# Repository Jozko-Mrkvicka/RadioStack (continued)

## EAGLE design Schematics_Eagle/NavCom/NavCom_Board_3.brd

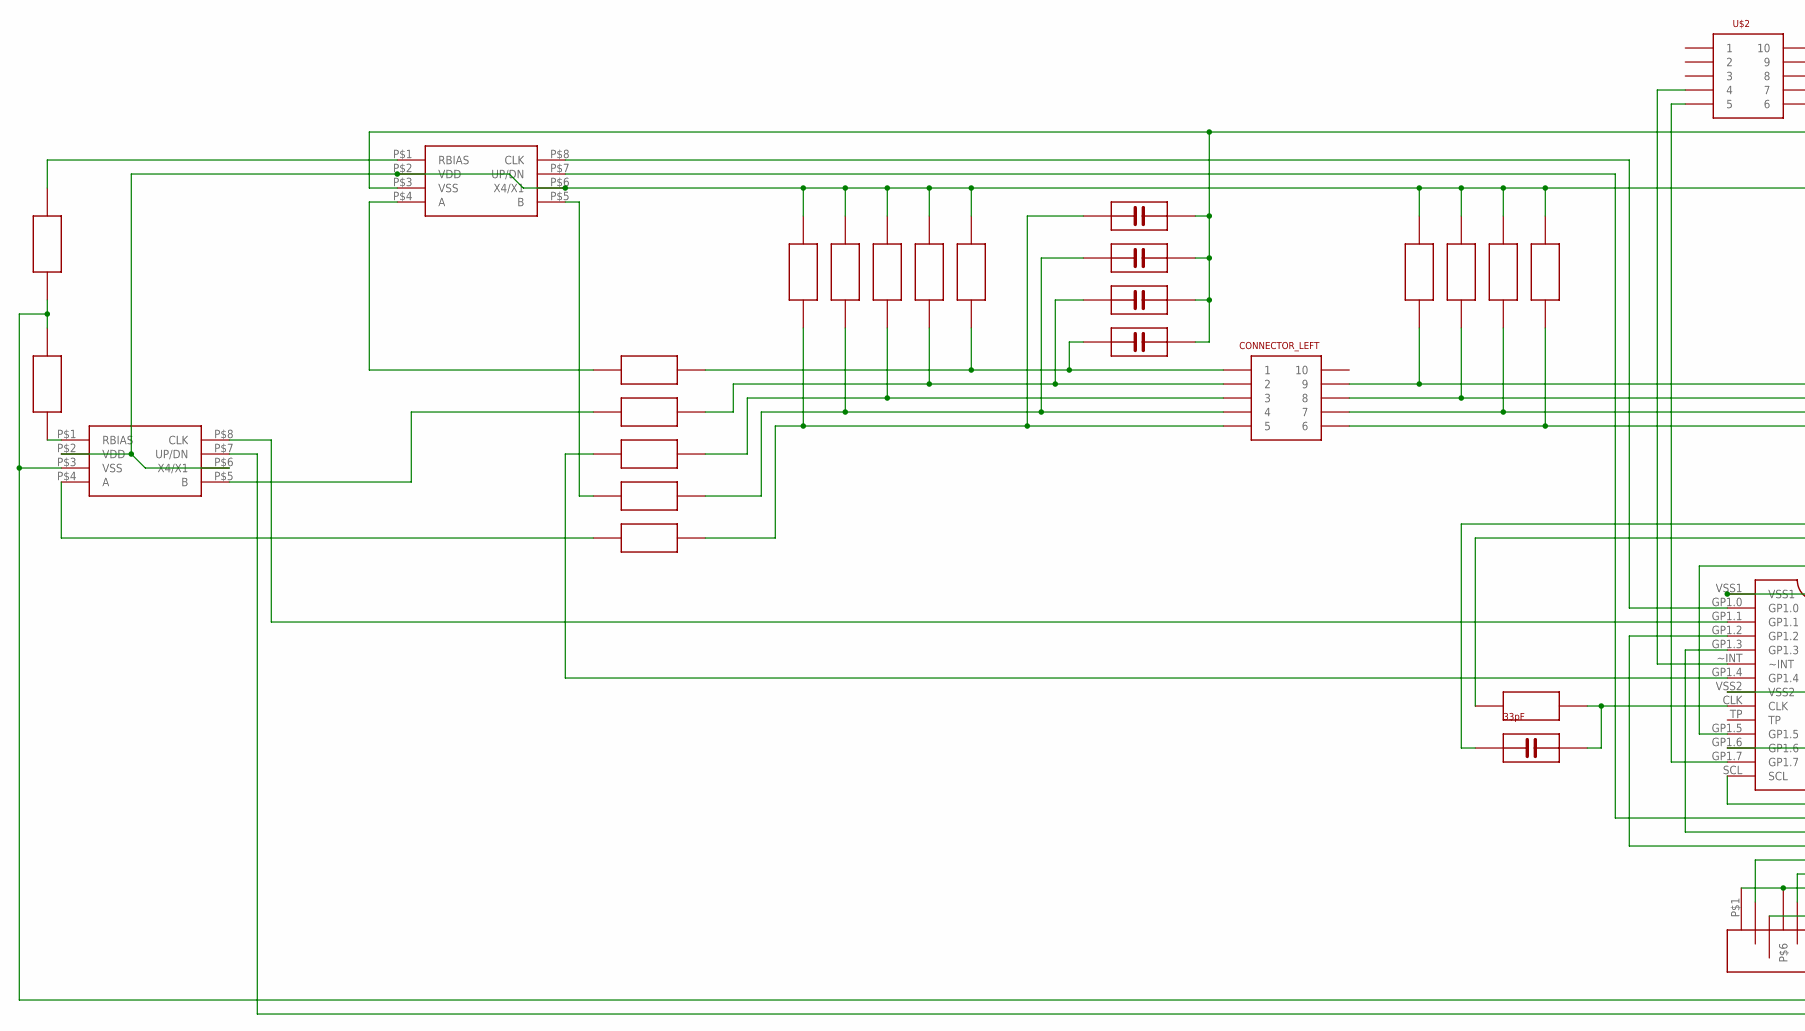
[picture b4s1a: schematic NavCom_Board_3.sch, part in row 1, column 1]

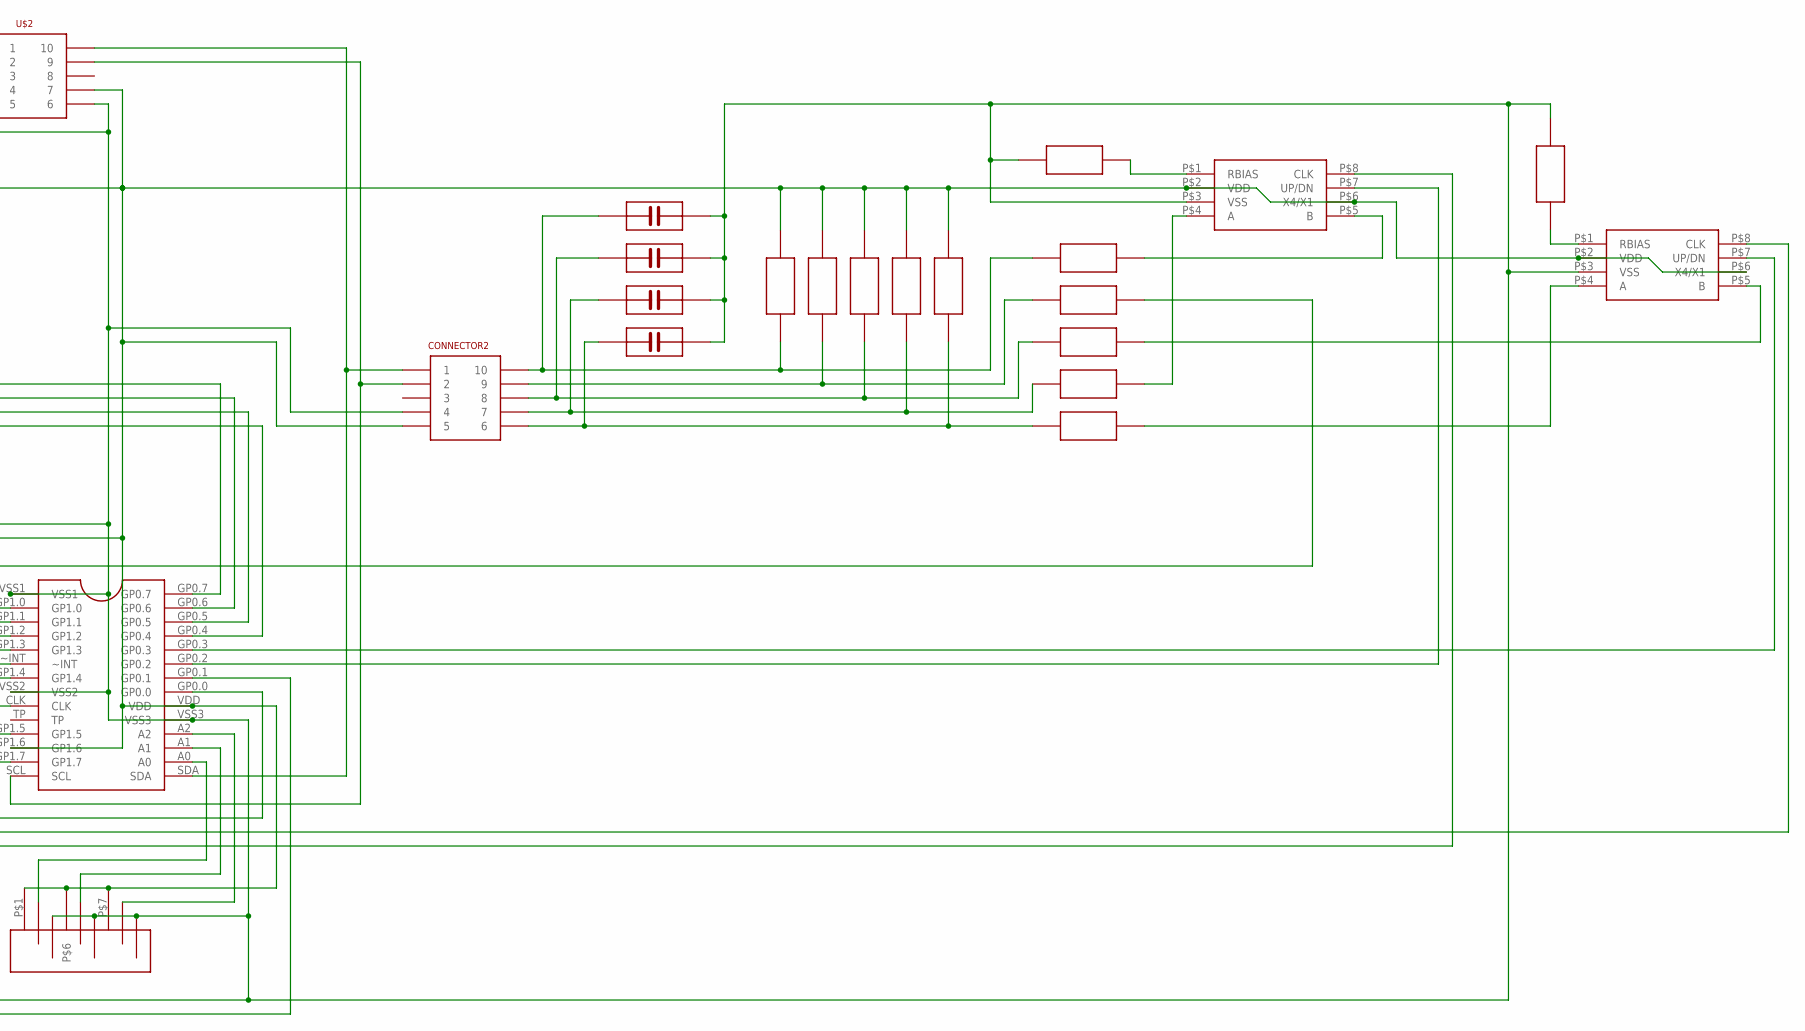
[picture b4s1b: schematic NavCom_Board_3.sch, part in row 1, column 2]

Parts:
33PF: 33pF; KONDENZATOR
CONNECTOR2: LISTA_2X5
CONNECTOR_LEFT: LISTA_2X5
U$1: MCP23016
U$2: LISTA_2X5
U$3, U$4, U$5, U$6: LS7084
U$7, U$9, U$10, U$13, U$14, U$15, U$17, U$18, U$19, U$20, U$21, U$22, U$30, U$31, U$32, U$33, U$36, U$38, U$39: REZISTOR
U$8, U$12, U$16: 470Ω; REZISTOR
U$11: ADRESA_0..2
U$23: 3.9k; REZISTOR
U$24, U$44: 103; KONDENZATOR
U$25, U$26, U$28, U$37, U$42, U$43: KONDENZATOR
U$27, U$34, U$40, U$41: 470M; REZISTOR
U$29, U$35: 4.7k; REZISTOR

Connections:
unnamed: CONNECTOR2.10, U$7.P$1, U$29.P$2, U$37.P$1
unnamed: CONNECTOR2.9, U$9.P$1, U$30.P$2
unnamed: CONNECTOR2.8, U$10.P$1, U$31.P$2, U$42.P$1
unnamed: CONNECTOR2.6, U$12.P$1, U$33.P$2, U$44.P$1
unnamed: U$5.P$4 (A), U$33.P$1
unnamed: CONNECTOR2.7, U$17.P$1, U$32.P$2, U$43.P$1
unnamed: 33PF.P$1, CONNECTOR2.4, U$1.VSS1, U$1.VSS2, U$1.VSS3, U$2.6, U$3.P$3 (VSS), U$4.P$3 (VSS), U$5.P$3 (VSS), U$6.P$3 (VSS), U$11.P$3, U$11.P$4, U$11.P$9, U$24.P$2, U$25.P$2, U$26.P$2, U$27.P$2, U$28.P$2, U$34.P$1, U$37.P$2, U$40.P$1, U$41.P$1, U$42.P$2, U$43.P$2, U$44.P$2
unnamed: CONNECTOR2.5, U$1.GP1.6, U$1.VDD, U$2.7, U$3.P$2 (VDD), U$3.P$6 (X4/X1), U$4.P$2 (VDD), U$4.P$6 (X4/X1), U$5.P$2 (VDD), U$5.P$6 (X4/X1), U$6.P$2 (VDD), U$6.P$6 (X4/X1), U$7.P$2, U$8.P$1, U$9.P$2, U$10.P$2, U$11.P$1, U$11.P$6, U$11.P$7, U$12.P$2, U$13.P$1, U$14.P$1, U$15.P$1, U$16.P$1, U$17.P$2, U$18.P$1, U$19.P$1, U$20.P$1, U$21.P$1, U$23.P$1
unnamed: CONNECTOR_LEFT.1, U$16.P$2, U$24.P$1, U$35.P$2
unnamed: CONNECTOR_LEFT.2, U$13.P$2, U$25.P$1, U$36.P$2
unnamed: U$1.GP1.4, U$22.P$1
unnamed: CONNECTOR_LEFT.4, U$15.P$2, U$26.P$1, U$38.P$2
unnamed: CONNECTOR_LEFT.5, U$18.P$2, U$28.P$1, U$39.P$2
unnamed: U$6.P$4 (A), U$39.P$1
unnamed: U$4.P$4 (A), U$32.P$1
unnamed: CONNECTOR_LEFT.9, U$1.GP0.7, U$8.P$2
unnamed: U$5.P$5 (B), U$31.P$1
unnamed: U$1.GP1.5, U$30.P$1
unnamed: U$4.P$5 (B), U$29.P$1
unnamed: U$3.P$4 (A), U$35.P$1
unnamed: CONNECTOR_LEFT.3, U$14.P$2, U$22.P$2
unnamed: U$4.P$1 (RBIAS), U$27.P$1
unnamed: U$6.P$5 (B), U$36.P$1
unnamed: U$1.GP0.2, U$4.P$7 (UP/DN)
unnamed: U$1.GP1.2, U$4.P$8 (CLK)
unnamed: U$1.A2, U$11.P$8
unnamed: U$3.P$1 (RBIAS), U$40.P$2
unnamed: U$5.P$1 (RBIAS), U$34.P$2
unnamed: CONNECTOR_LEFT.8, U$1.GP0.6, U$19.P$2
unnamed: U$1.GP0.3, U$5.P$7 (UP/DN)
unnamed: U$1.GP1.3, U$5.P$8 (CLK)
unnamed: U$1.GP1.0, U$3.P$8 (CLK)
unnamed: U$1.GP0.0, U$3.P$7 (UP/DN)
unnamed: U$1.GP1.1, U$6.P$8 (CLK)
unnamed: U$6.P$1 (RBIAS), U$41.P$2
unnamed: U$1.A1, U$11.P$5
unnamed: U$1.GP0.1, U$6.P$7 (UP/DN)
unnamed: U$1.A0, U$11.P$2
unnamed: 33PF.P$2, U$1.CLK, U$23.P$2
unnamed: CONNECTOR2.1, U$1.SDA, U$2.10
unnamed: CONNECTOR2.2, U$1.SCL, U$2.9
unnamed: U$1.~INT, U$2.4
unnamed: CONNECTOR_LEFT.7, U$1.GP0.5, U$20.P$2
unnamed: U$1.GP1.7, U$2.5
unnamed: CONNECTOR_LEFT.6, U$1.GP0.4, U$21.P$2
unnamed: U$3.P$5 (B), U$38.P$1

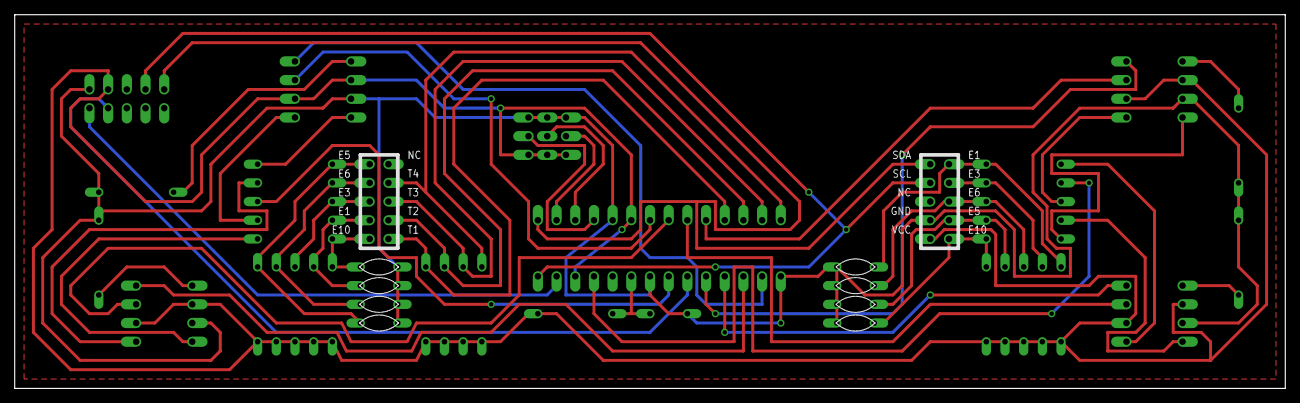
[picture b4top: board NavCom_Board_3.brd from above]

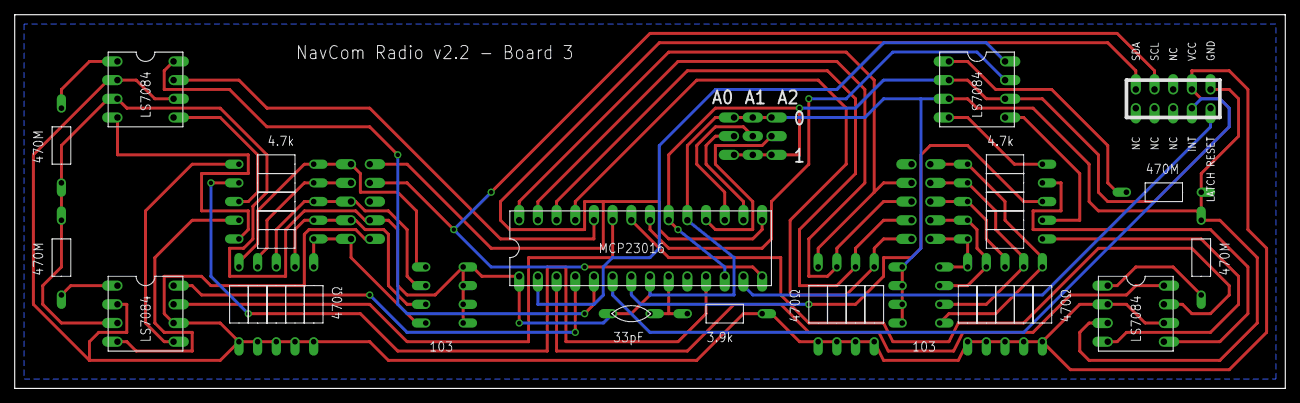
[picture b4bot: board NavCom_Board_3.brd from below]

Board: 2 copper layers, 172.7 x 50.8 mm, 47 parts (36 on the bottom side), 46 nets.

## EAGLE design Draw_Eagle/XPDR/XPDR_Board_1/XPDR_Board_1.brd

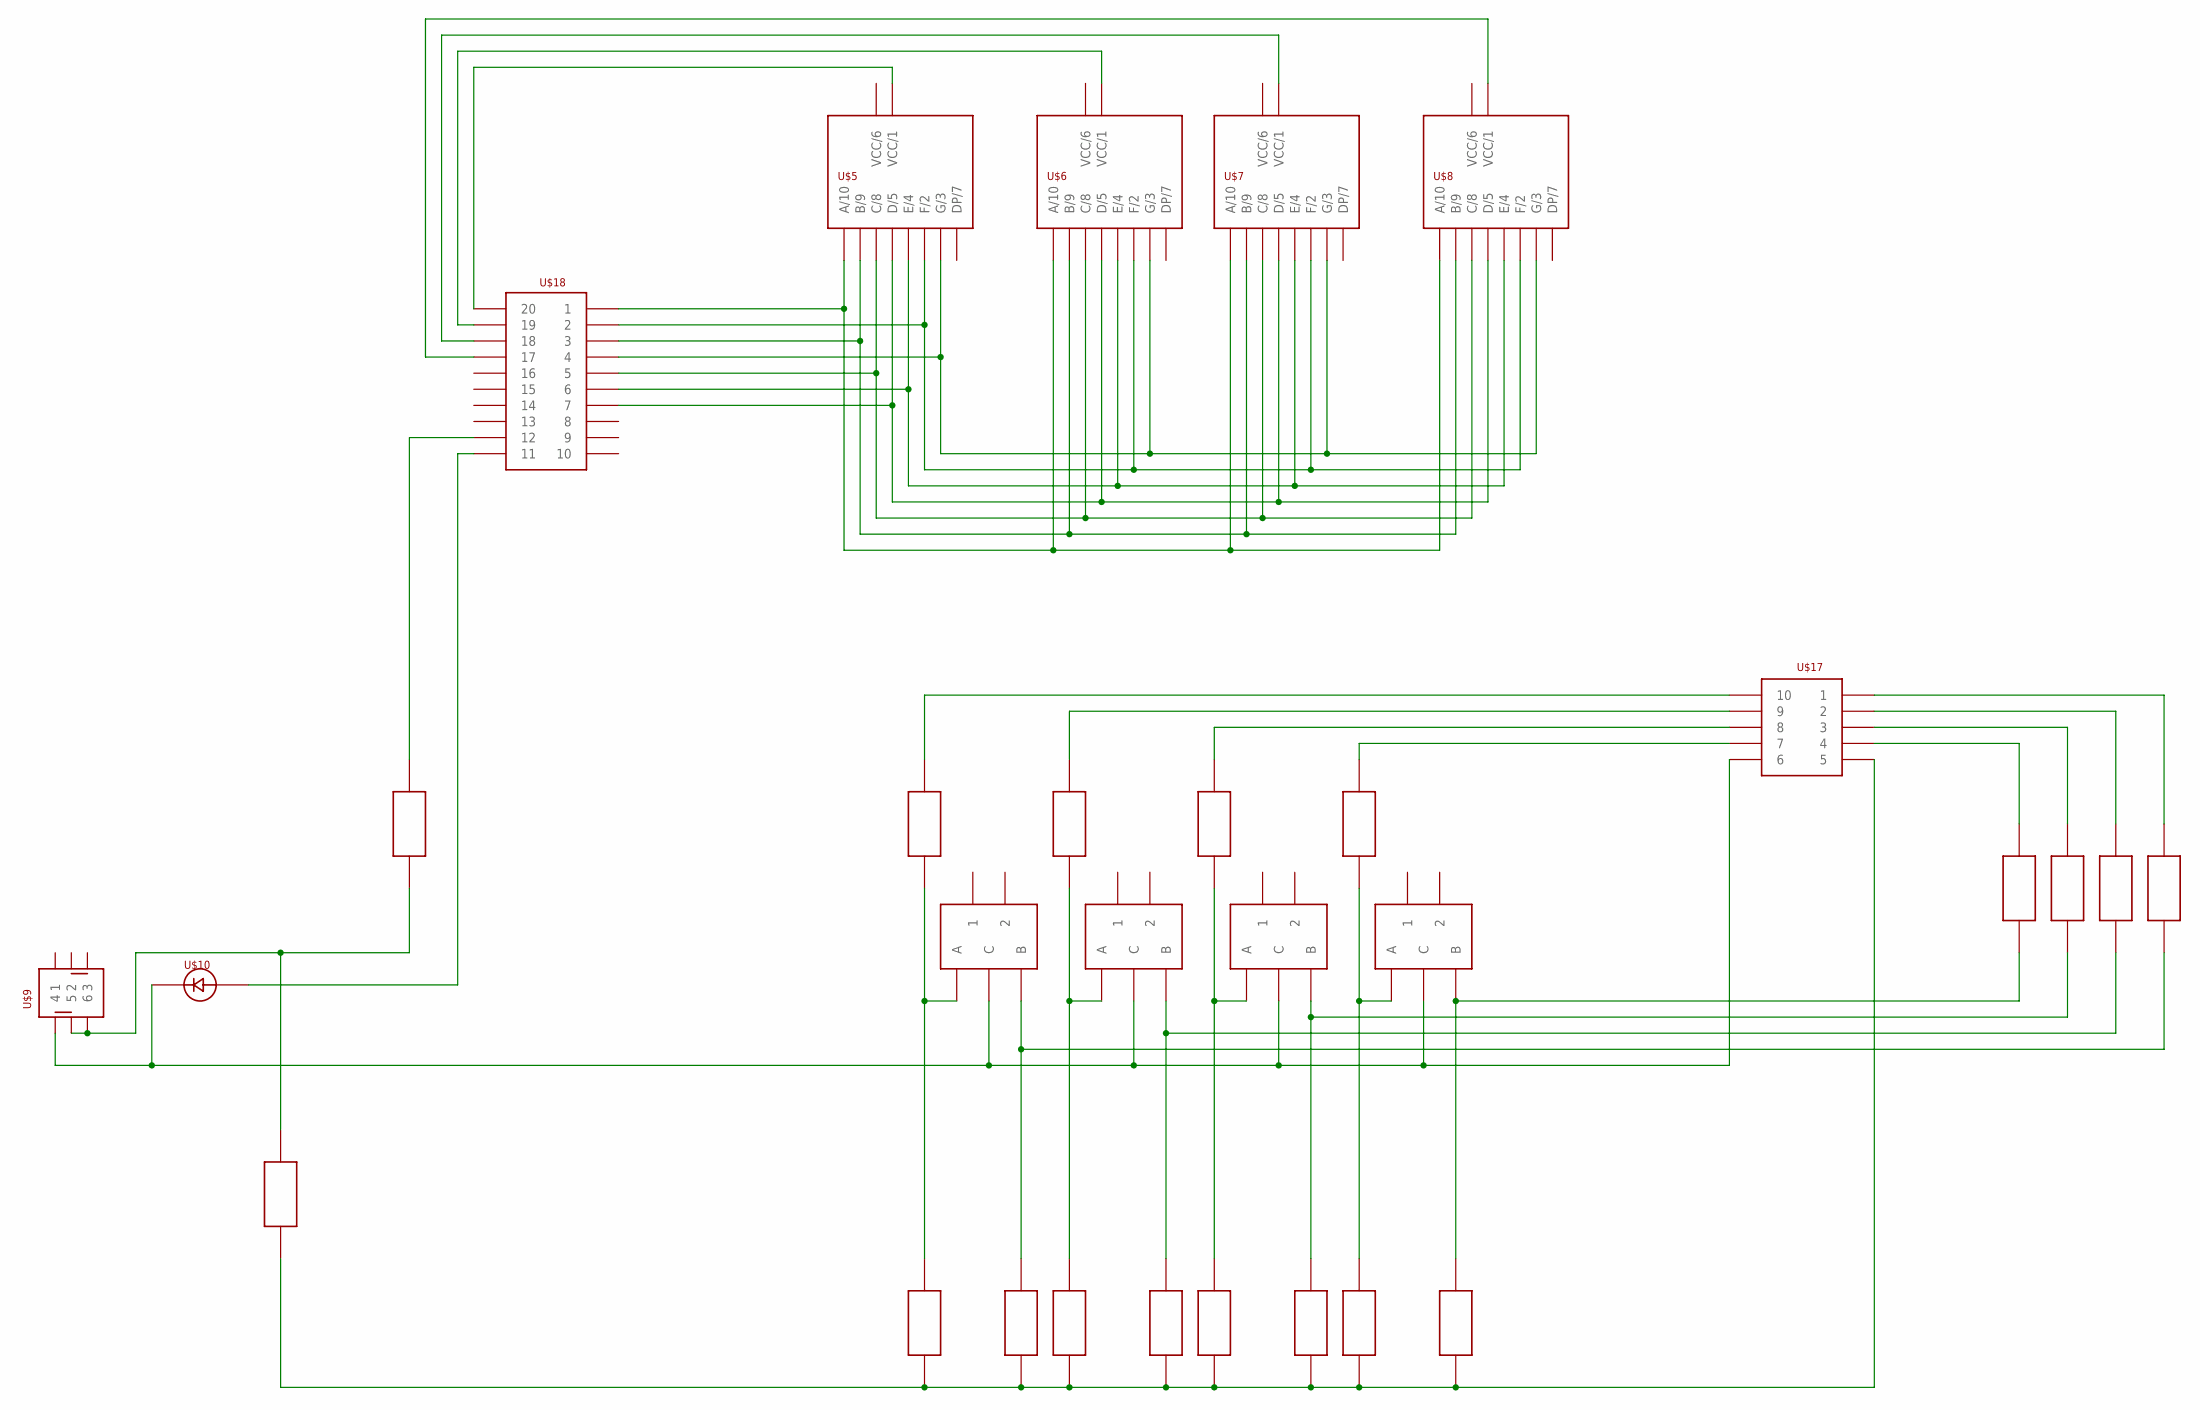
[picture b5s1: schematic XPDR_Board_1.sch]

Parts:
U$1, U$2, U$3, U$4: PEC11R
U$5, U$6, U$7, U$8: SA3611EWA
U$9: P1-0S
U$10: LED_5MM
U$11, U$12, U$13, U$14, U$15, U$16, U$19, U$20, U$21, U$22, U$23, U$24, U$25, U$26, U$27, U$28, U$30, U$31: REZISTOR
U$17: LISTA_2X5
U$18: LISTA_2X10

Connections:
unnamed: U$5.10 (A/10), U$6.10 (A/10), U$7.10 (A/10), U$8.10 (A/10), U$18.1
unnamed: U$5.9 (B/9), U$6.9 (B/9), U$7.9 (B/9), U$8.9 (B/9), U$18.3
unnamed: U$5.8 (C/8), U$6.8 (C/8), U$7.8 (C/8), U$8.8 (C/8), U$18.5
unnamed: U$5.5 (D/5), U$6.5 (D/5), U$7.5 (D/5), U$8.5 (D/5), U$18.7
unnamed: U$11.P$2, U$17.10
unnamed: U$5.2 (F/2), U$6.2 (F/2), U$7.2 (F/2), U$8.2 (F/2), U$18.2
unnamed: U$5.3 (G/3), U$6.3 (G/3), U$7.3 (G/3), U$8.3 (G/3), U$18.4
unnamed: U$1.B, U$12.P$1, U$27.P$1
unnamed: U$5.4 (E/4), U$6.4 (E/4), U$7.4 (E/4), U$8.4 (E/4), U$18.6
unnamed: U$13.P$2, U$17.9
unnamed: U$2.B, U$14.P$1, U$25.P$1
unnamed: U$15.P$2, U$17.8
unnamed: U$3.B, U$16.P$1, U$23.P$1
unnamed: U$17.7, U$19.P$2
unnamed: U$4.B, U$20.P$1, U$21.P$1
unnamed: U$5.1 (VCC/1), U$18.20
unnamed: U$6.1 (VCC/1), U$18.19
unnamed: U$7.1 (VCC/1), U$18.18
unnamed: U$8.1 (VCC/1), U$18.17
unnamed: U$9.5, U$9.6, U$30.P$2, U$31.P$1
unnamed: U$1.C, U$2.C, U$3.C, U$4.C, U$9.4, U$10.P$2, U$17.6
unnamed: U$1.A, U$11.P$1, U$28.P$1
unnamed: U$12.P$2, U$17.1
unnamed: U$17.5, U$21.P$2, U$22.P$2, U$23.P$2, U$24.P$2, U$25.P$2, U$26.P$2, U$27.P$2, U$28.P$2, U$31.P$2
unnamed: U$3.A, U$15.P$1, U$24.P$1
unnamed: U$10.P$1, U$18.11
unnamed: U$4.A, U$19.P$1, U$22.P$1
unnamed: U$14.P$2, U$17.2
unnamed: U$16.P$2, U$17.3
unnamed: U$17.4, U$20.P$2
unnamed: U$2.A, U$13.P$1, U$26.P$1
unnamed: U$18.12, U$30.P$1

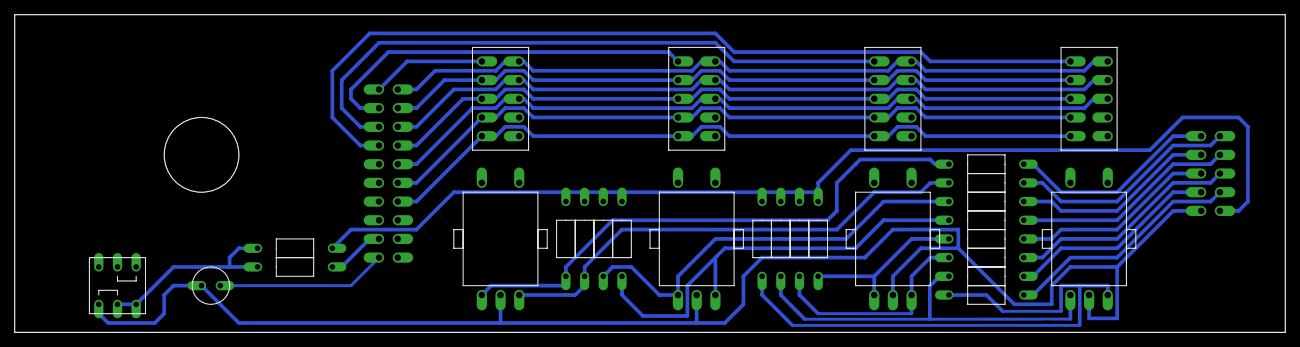
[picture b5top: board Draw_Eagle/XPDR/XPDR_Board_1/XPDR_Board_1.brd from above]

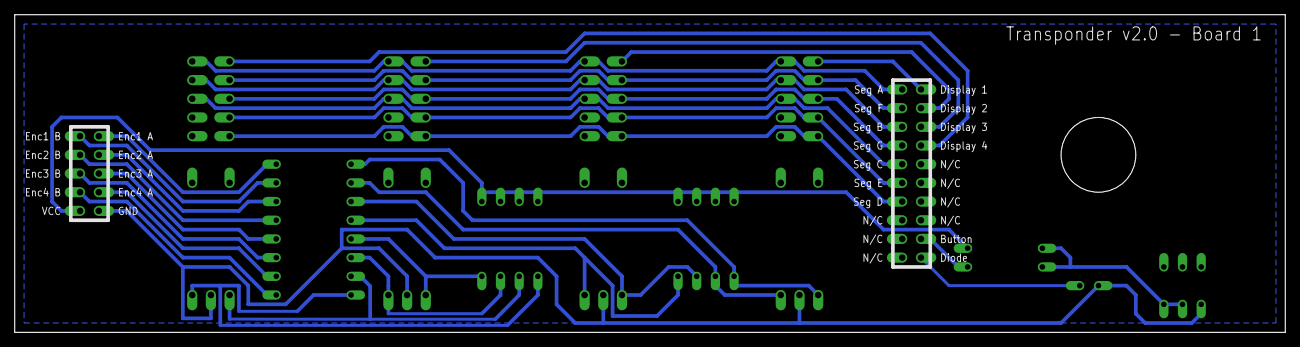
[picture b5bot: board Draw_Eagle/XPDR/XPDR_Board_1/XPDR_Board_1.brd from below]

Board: 2 copper layers, 172.7 x 43.2 mm, 30 parts (2 on the bottom side), 32 nets.

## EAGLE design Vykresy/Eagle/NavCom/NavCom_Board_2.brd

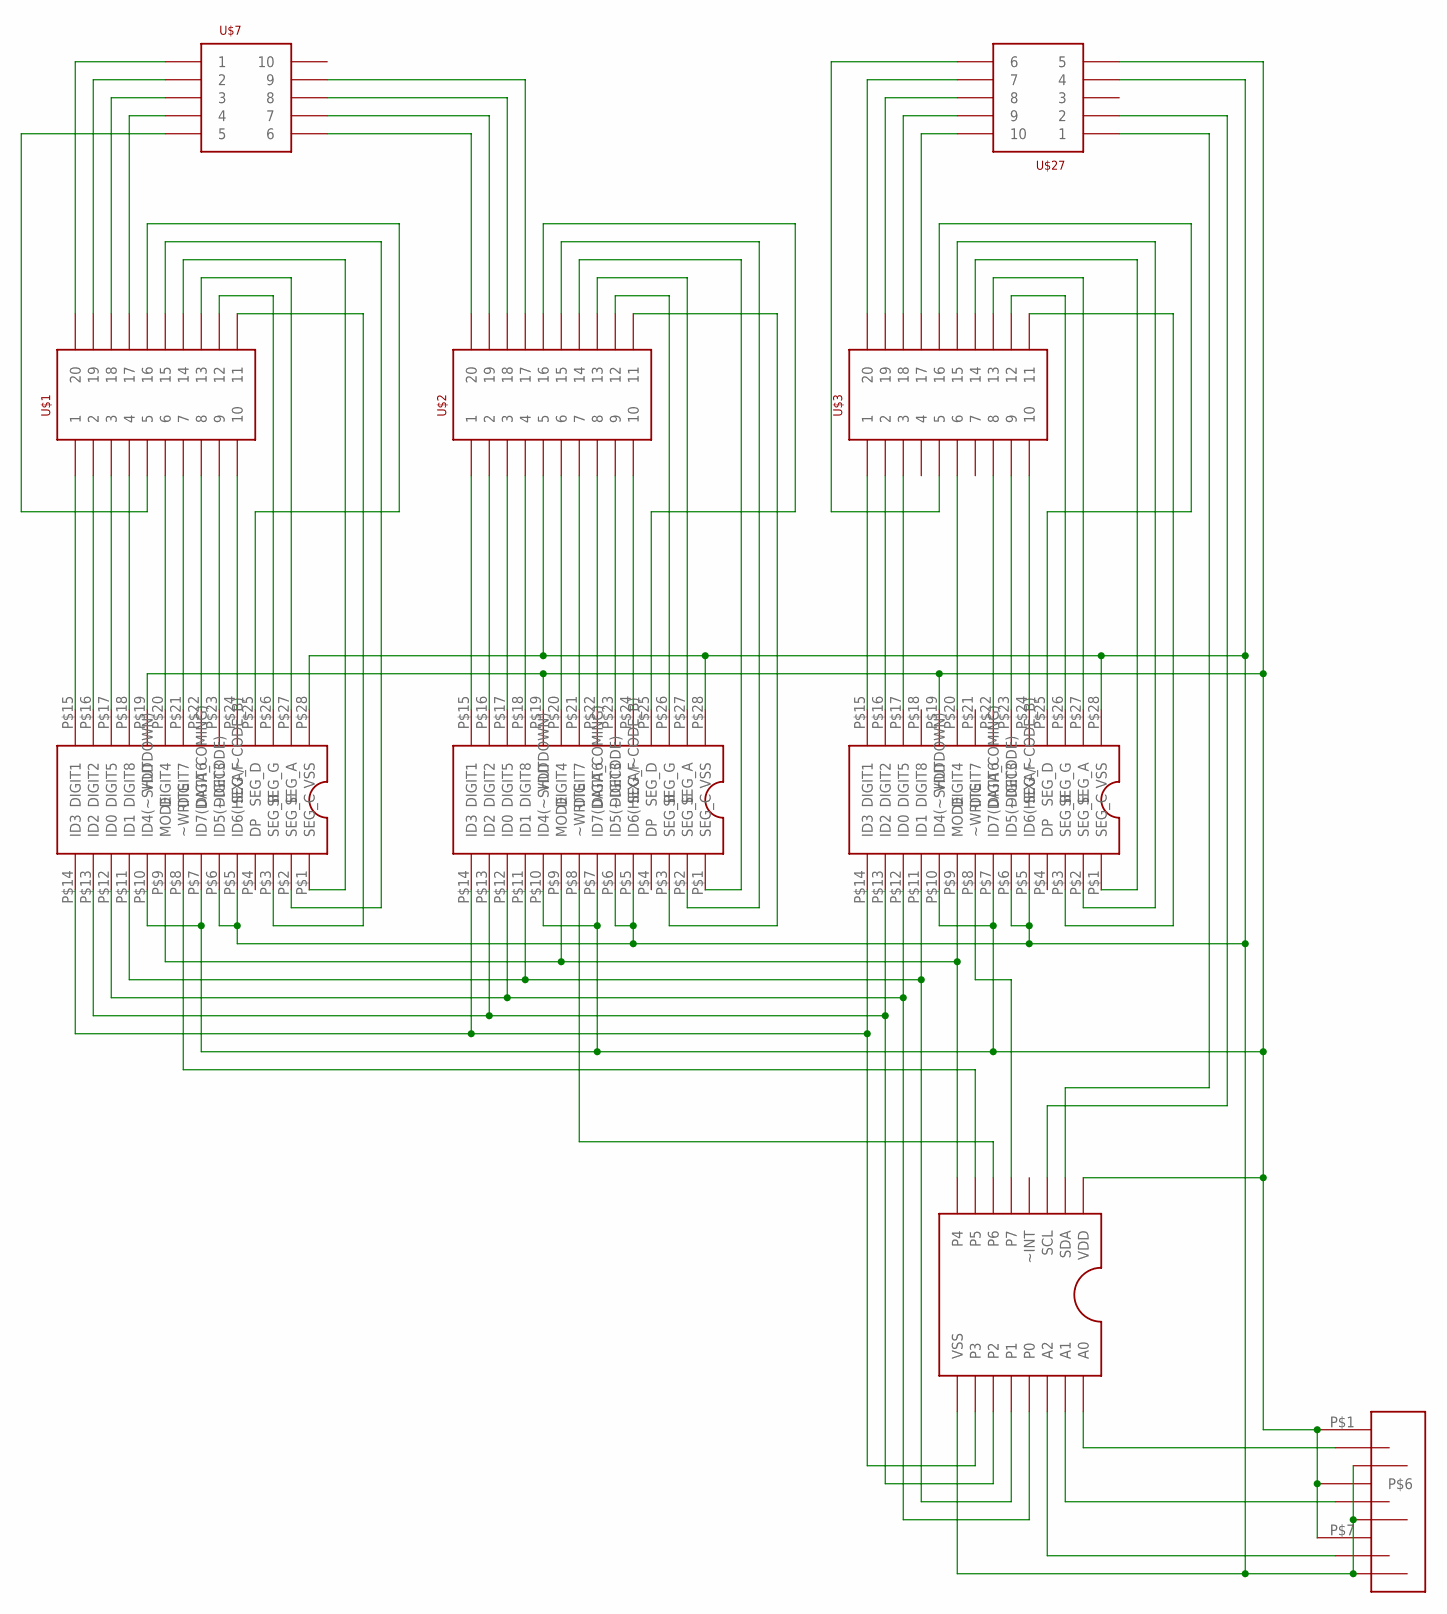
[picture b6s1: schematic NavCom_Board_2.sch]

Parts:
U$1, U$2, U$3: LISTA_2X10
U$4, U$5, U$6: ICM7228A
U$7, U$27: LISTA_2X5
U$9: PCF8574A
U$11: ADRESA_0..2

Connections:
GND: U$2.5, U$4.P$5 (ID6(HEXA/~CODE_B)), U$4.P$6 (ID5(~DECODE)), U$4.P$28 (VSS), U$5.P$5 (ID6(HEXA/~CODE_B)), U$5.P$6 (ID5(~DECODE)), U$5.P$28 (VSS), U$6.P$5 (ID6(HEXA/~CODE_B)), U$6.P$6 (ID5(~DECODE)), U$6.P$28 (VSS), U$9.VSS, U$11.P$3, U$11.P$4, U$11.P$9, U$27.4
unnamed: U$1.1, U$4.P$15 (DIGIT1)
unnamed: U$2.1, U$5.P$15 (DIGIT1)
unnamed: U$1.2, U$4.P$16 (DIGIT2)
unnamed: U$1.3, U$4.P$17 (DIGIT5)
unnamed: U$1.4, U$4.P$18 (DIGIT8)
unnamed: U$1.11, U$4.P$3 (SEG_B)
unnamed: U$1.6, U$4.P$20 (DIGIT4)
unnamed: U$1.7, U$4.P$21 (DIGIT7)
unnamed: U$1.8, U$4.P$22 (DIGIT6)
unnamed: U$1.9, U$4.P$23 (DIGIT3)
unnamed: U$1.10, U$4.P$24 (SEG_F)
unnamed: U$1.12, U$4.P$26 (SEG_G)
unnamed: U$1.13, U$4.P$27 (SEG_A)
unnamed: U$2.2, U$5.P$16 (DIGIT2)
unnamed: U$2.3, U$5.P$17 (DIGIT5)
unnamed: U$2.4, U$5.P$18 (DIGIT8)
unnamed: U$3.1, U$6.P$15 (DIGIT1)
unnamed: U$2.6, U$5.P$20 (DIGIT4)
unnamed: U$2.7, U$5.P$21 (DIGIT7)
unnamed: U$2.8, U$5.P$22 (DIGIT6)
unnamed: U$2.9, U$5.P$23 (DIGIT3)
unnamed: U$2.10, U$5.P$24 (SEG_F)
unnamed: U$3.2, U$6.P$16 (DIGIT2)
unnamed: U$3.3, U$6.P$17 (DIGIT5)
unnamed: U$3.6, U$6.P$20 (DIGIT4)
unnamed: U$3.8, U$6.P$22 (DIGIT6)
unnamed: U$3.9, U$6.P$23 (DIGIT3)
unnamed: U$3.10, U$6.P$24 (SEG_F)
unnamed: U$2.16, U$5.P$25 (SEG_D)
unnamed: U$2.12, U$5.P$26 (SEG_G)
unnamed: U$2.13, U$5.P$27 (SEG_A)
unnamed: U$3.16, U$6.P$25 (SEG_D)
unnamed: U$3.12, U$6.P$26 (SEG_G)
unnamed: U$3.13, U$6.P$27 (SEG_A)
unnamed: U$1.14, U$4.P$1 (SEG_C)
unnamed: U$1.15, U$4.P$2 (SEG_E)
unnamed: U$1.16, U$4.P$25 (SEG_D)
unnamed: U$4.P$14 (ID3), U$5.P$14 (ID3), U$6.P$14 (ID3), U$9.P3
unnamed: U$4.P$13 (ID2), U$5.P$13 (ID2), U$6.P$13 (ID2), U$9.P2
unnamed: U$4.P$12 (ID0), U$5.P$12 (ID0), U$6.P$12 (ID0), U$9.P0
unnamed: U$4.P$11 (ID1), U$5.P$11 (ID1), U$6.P$11 (ID1), U$9.P1
unnamed: U$4.P$9 (MODE), U$5.P$9 (MODE), U$6.P$9 (MODE), U$9.P4
unnamed: U$2.14, U$5.P$1 (SEG_C)
unnamed: U$2.15, U$5.P$2 (SEG_E)
unnamed: U$9.A0, U$11.P$2
unnamed: U$3.14, U$6.P$1 (SEG_C)
unnamed: U$3.15, U$6.P$2 (SEG_E)
unnamed: U$9.A1, U$11.P$5
unnamed: U$3.11, U$6.P$3 (SEG_B)
unnamed: U$2.11, U$5.P$3 (SEG_B)
unnamed: U$9.A2, U$11.P$8
unnamed: U$6.P$8 (~WRITE), U$9.P7
unnamed: U$5.P$8 (~WRITE), U$9.P6
unnamed: U$4.P$8 (~WRITE), U$9.P5
unnamed: U$1.20, U$7.1
unnamed: U$4.P$7 (ID7(DATA_COMING)), U$4.P$10 (ID4(~SHUTDOWN)), U$4.P$19 (VDD), U$5.P$7 (ID7(DATA_COMING)), U$5.P$10 (ID4(~SHUTDOWN)), U$5.P$19 (VDD), U$6.P$7 (ID7(DATA_COMING)), U$6.P$10 (ID4(~SHUTDOWN)), U$6.P$19 (VDD), U$9.VDD, U$11.P$1, U$11.P$6, U$11.P$7, U$27.5
unnamed: U$1.19, U$7.2
unnamed: U$1.18, U$7.3
unnamed: U$1.17, U$7.4
unnamed: U$1.5, U$7.5
unnamed: U$2.20, U$7.6
unnamed: U$2.19, U$7.7
unnamed: U$2.18, U$7.8
unnamed: U$2.17, U$7.9
unnamed: U$9.SDA, U$27.1
unnamed: U$9.SCL, U$27.2
unnamed: U$3.17, U$27.10
unnamed: U$3.18, U$27.9
unnamed: U$3.5, U$27.6
unnamed: U$3.19, U$27.8
unnamed: U$3.20, U$27.7

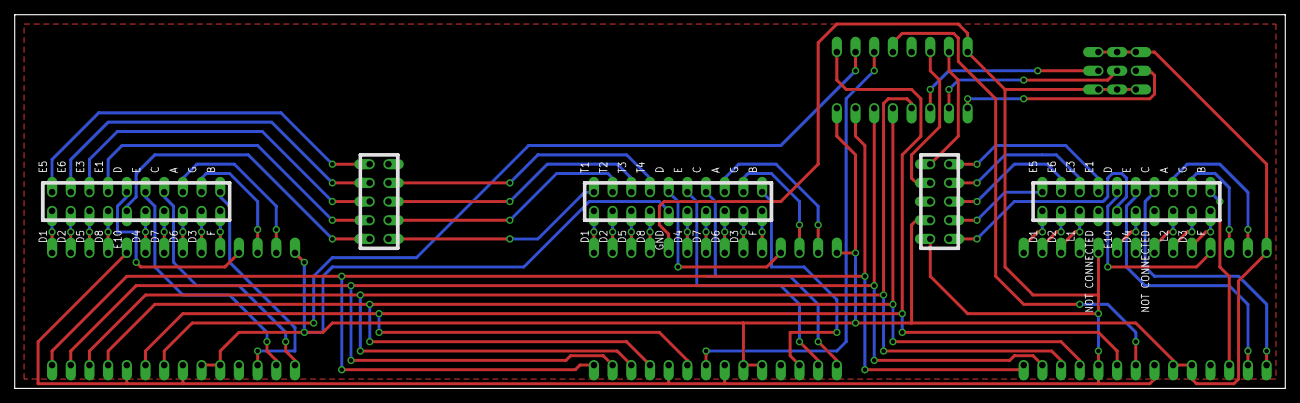
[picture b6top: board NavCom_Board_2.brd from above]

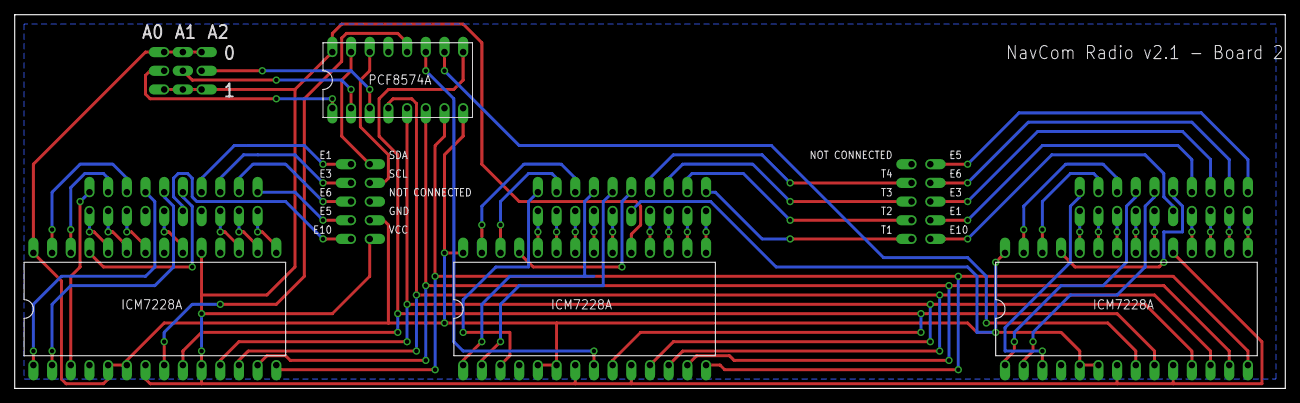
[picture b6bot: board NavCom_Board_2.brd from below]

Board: 2 copper layers, 172.7 x 50.8 mm, 10 parts (4 on the bottom side), 72 nets.
